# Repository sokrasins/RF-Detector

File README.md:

# RF Detector

Current verion: R2

Note: the schematic and layout were lost for R2, but the gerbers are included in the folder

## Usage

Connect power (pins 1 & 2), RF in and out, and scope/logic analyzer on pin 3 and/or 4.

## Pinout

  Pins:
  
  1. Gnd
  2. Vcc. Accepts 3V3 - 5V, haven't spec'd the limits here.
  3. Digi out - high (Vcc) when rf is detected above the threshold, low otherwise. The threshold is set by the voltage divider R2 and R5.
  4. Analog out - amplitude is proportional to the RF power in
  5. Gnd
  6. Gnd

  RF In - 5-10 dBm is a suitable range for digital out. RF in should be tolerant up to 30 dBm.

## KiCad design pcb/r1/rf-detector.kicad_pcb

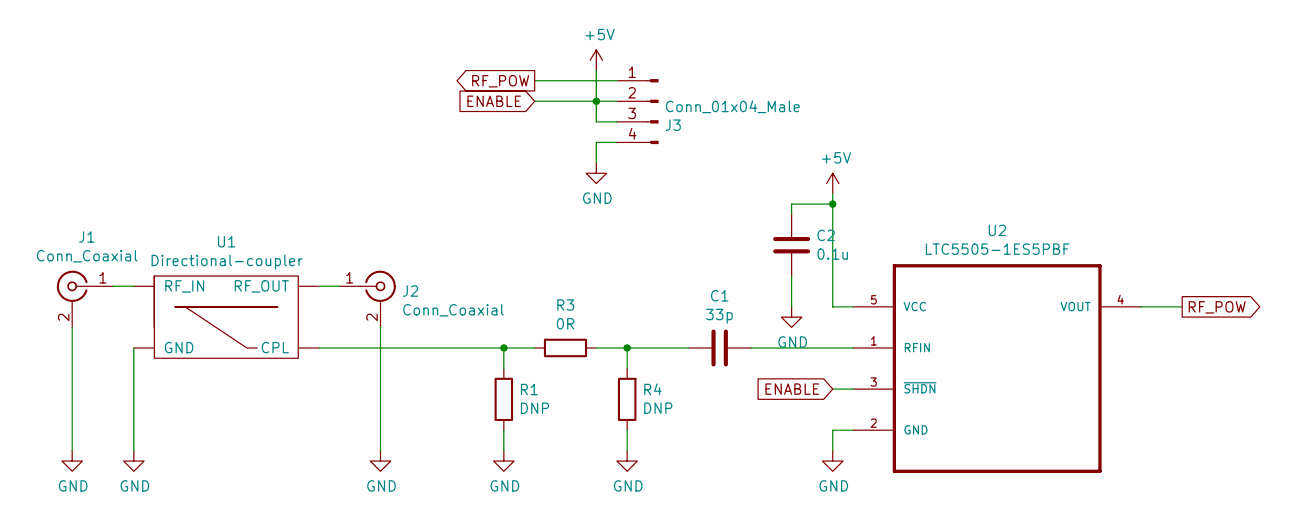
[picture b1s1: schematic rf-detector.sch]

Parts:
C1: 33p; C_0603_1608Metric
C2: 0.1u; C_0603_1608Metric
J1, J2: Conn_Coaxial; SMA_Samtec_SMA-J-P-X-ST-EM1_EdgeMount
J3: Conn_01x04_Male; PinHeader_1x04_P2.54mm_Horizontal
R1, R4: DNP; R_0603_1608Metric
R3: 0R; R_0603_1608Metric
U1: Directional-coupler; D17W+
U2: LTC5505-1ES5PBF; SOT95P280X100-5N

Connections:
ENABLE: C2.2, J3.2, J3.3, U2.3 (~SHDN), U2.5 (VCC)
GND: C2.1, J1.2 (Ext), J2.2 (Ext), J3.4, R1.2, R4.1, U1.1 (GND), U1.2 (GND), U1.5 (GND), U2.2 (GND)
unnamed: C1.1, U2.1 (RFIN)
unnamed: C1.2, R3.1, R4.2
unnamed: J1.1 (In), U1.4 (RF_IN)
unnamed: J2.1 (In), U1.6 (RF_OUT)
unnamed: R1.1, R3.2, U1.3 (CPL)
RF_POW: J3.1, U2.4 (VOUT)

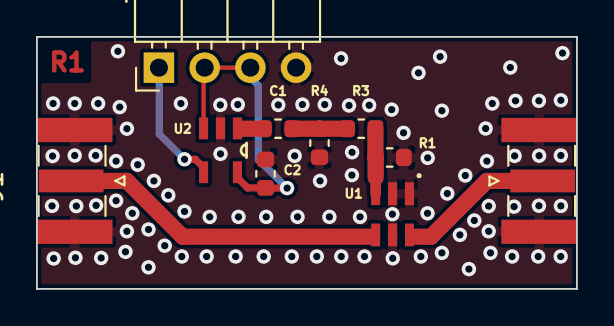
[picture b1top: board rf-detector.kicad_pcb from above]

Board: 2 copper layers, 30.0 x 14.0 mm, 10 parts (0 on the bottom side), 8 nets.

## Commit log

2024-07-26 Push existing designs and docs
2024-07-30 Update README.md
    Added max rf power spec
